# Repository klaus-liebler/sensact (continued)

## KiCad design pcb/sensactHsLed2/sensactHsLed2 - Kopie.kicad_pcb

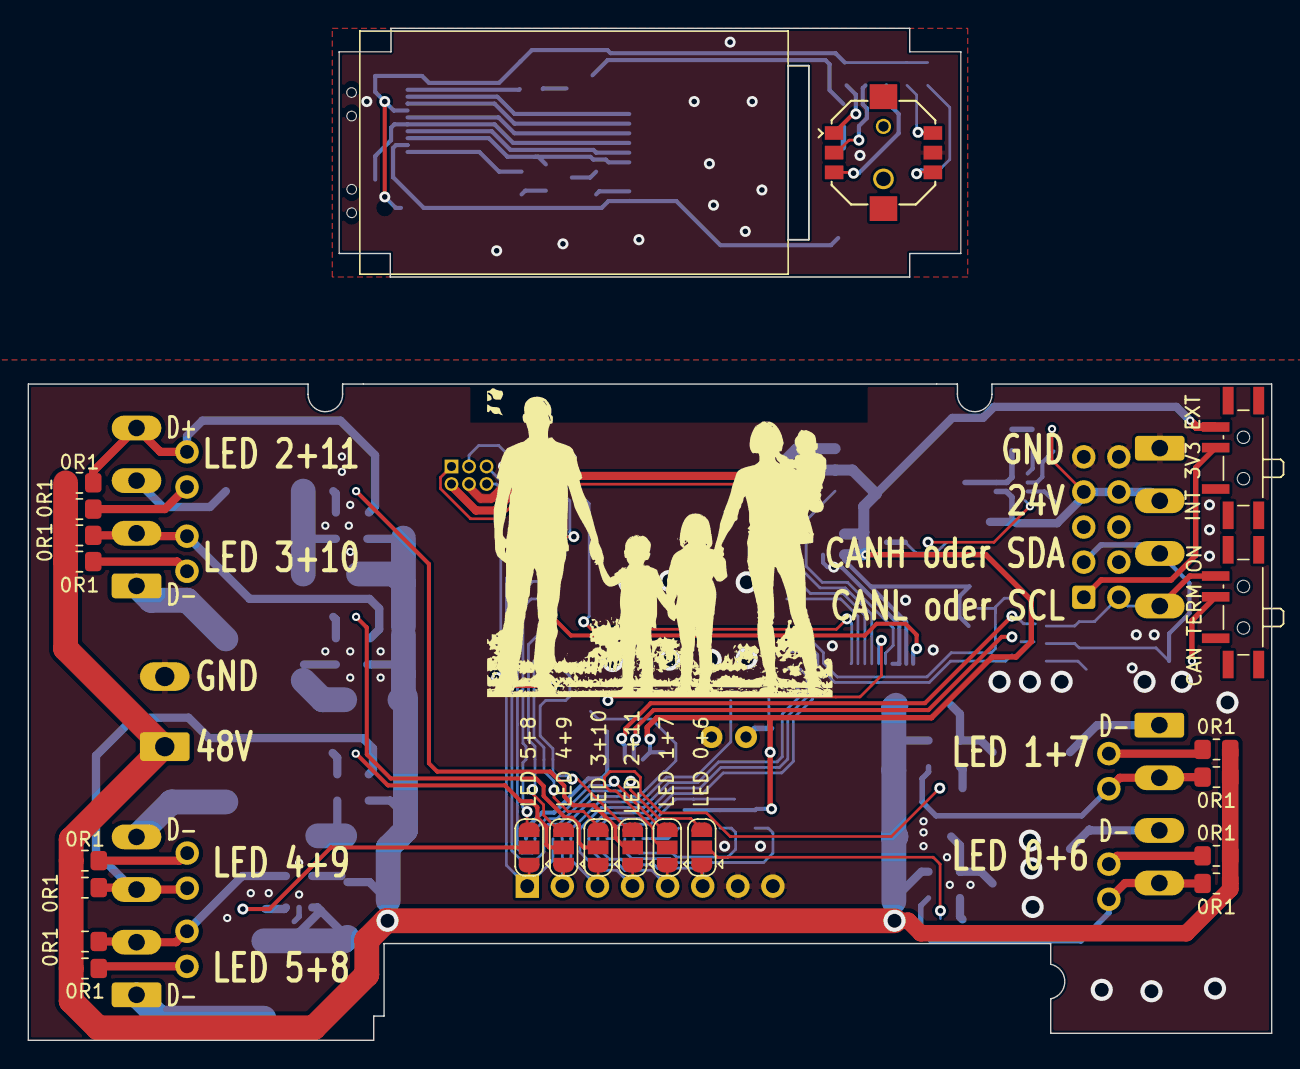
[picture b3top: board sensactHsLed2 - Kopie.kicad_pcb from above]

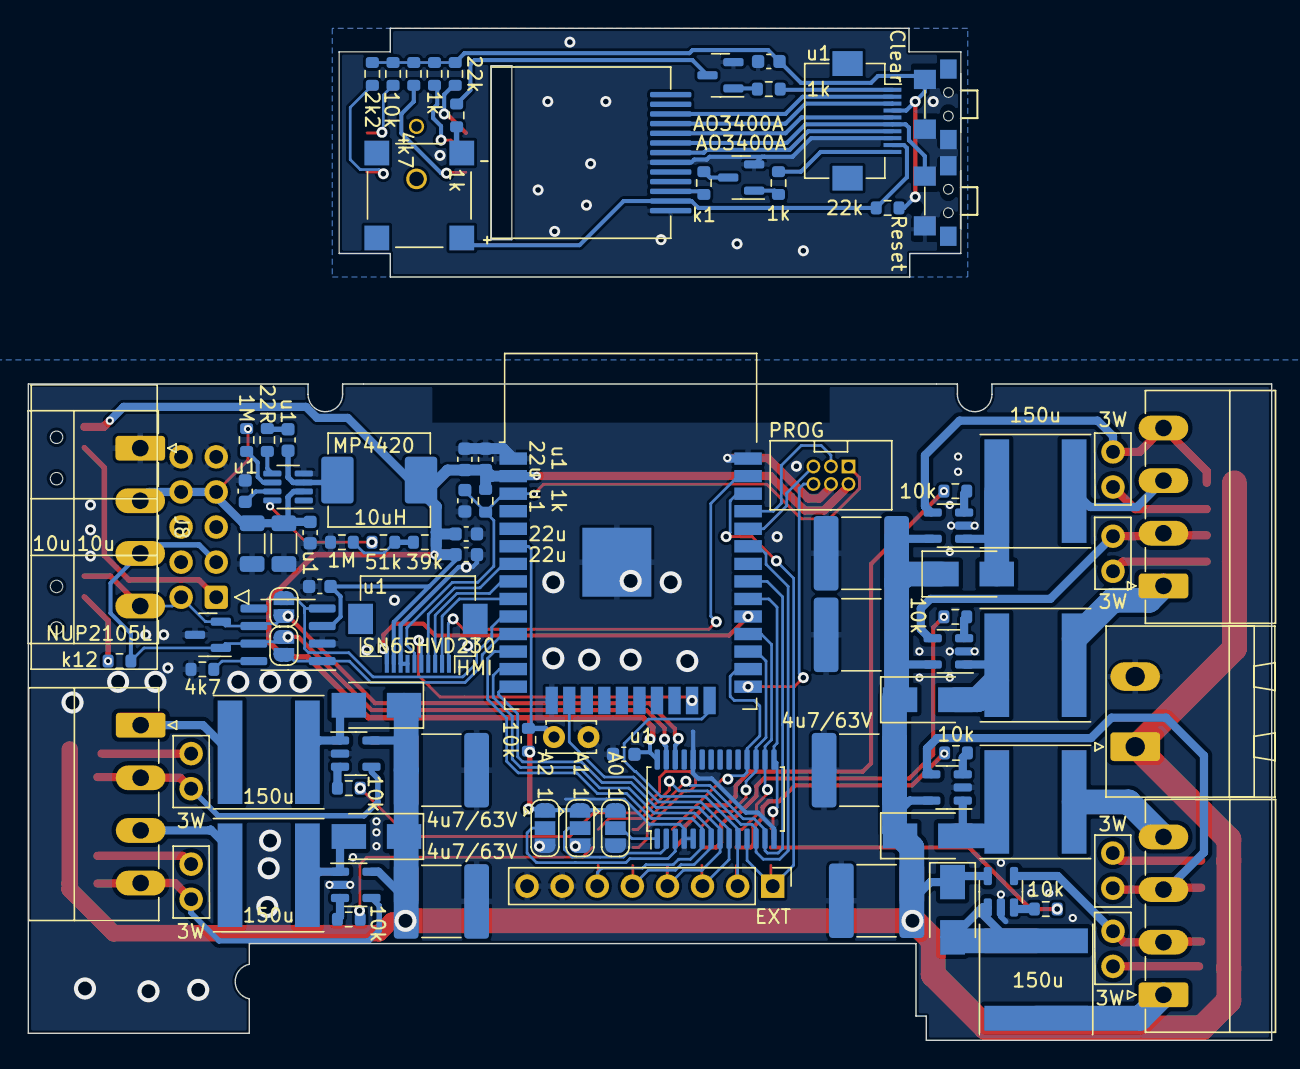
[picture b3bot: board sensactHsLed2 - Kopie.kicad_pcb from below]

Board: 2 copper layers, 90.0 x 47.5 mm, 118 parts (95 on the bottom side), 101 nets.

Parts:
BZ1: Buzzer; XDCR_CMT-7525-80-SMT-TR
C1, C10, C11: 22u; C_0603_1608Metric
C2, C3, C4, C7, C8, C9, C18, C19: u1; C_0603_1608Metric
C5, C6: 10u; C_1206_3216Metric
C12, C13, C14, C15, C16, C17: 4u7/63V; C_2220_5650Metric
D1: NUP2105L; SOT-23
D2, D3, D4, D5, D6, D7: D; D_SMA
IMG1: Family; family
J1: PROG; IDC_2x03_P1.27mm_Vertical
J2: EXT; PinHeader_1x08_P2.54mm_Vertical
J3, J4, J5: LED1+2; PhoenixContact_MC_1,5_4-G-3.81_1x04_P3.81mm_Horizontal
J6: Conn_01x02; PhoenixContact_MSTBA_2,5_2-G-5,08_1x02_P5.08mm_Horizontal
J7: SensactBusConnector; IDC-Header_2x05_P2.54mm_Horizontal
J8: POWER+CAN; PhoenixContact_MC_1,5_4-G-3.81_1x04_P3.81mm_Horizontal
J9: HMI; Hirose_FH12-10S-0.5SH_1x10-1MP_P0.50mm_Horizontal
J10: Conn_01x10; Hirose_FH12-10S-0.5SH_1x10-1MP_P0.50mm_Horizontal
JP1, JP2, JP3, JP4, JP5, JP6: 3W; Jumper 2x2.54
JP7: LED 0+6; SolderJumper-3_P1.3mm_Open_RoundedPad1.0x1.5mm
JP8: LED 1+7; SolderJumper-3_P1.3mm_Open_RoundedPad1.0x1.5mm
JP9: LED 2+11; SolderJumper-3_P1.3mm_Open_RoundedPad1.0x1.5mm
JP10: LED 3+10; SolderJumper-3_P1.3mm_Open_RoundedPad1.0x1.5mm
JP11: LED 4+9; SolderJumper-3_P1.3mm_Open_RoundedPad1.0x1.5mm
JP12: LED 5+8; SolderJumper-3_P1.3mm_Open_RoundedPad1.0x1.5mm
JP13, JP14: Jumper_2_Open; SolderJumper-2_P1.3mm_Open_RoundedPad1.0x1.5mm
L1: 10uH; L_Abracon_ASPI-0630LR
L2, L3, L4, L5, L6, L7: 150u; L_Taiyo-Yuden_NR-80xx
Q1, Q3: AO3400A; SOT-23
R1, R27, R34, R36, R37: 1k; R_0603_1608Metric
R2, R32: 4k7; R_0603_1608Metric
R3: k12; R_0603_1608Metric
R4, R7: 1M; R_0603_1608Metric
R5: 22R; R_0603_1608Metric
R6: 51k; R_0603_1608Metric
R8: 39k; R_0603_1608Metric
R9, R11, R13, R15, R17, R19, R31, R39: 10k; R_0603_1608Metric
R10, R12, R14, R16, R18, R20, R21, R22, R23, R24, R25, R26: 0R1; R_0805_2012Metric_Pad1.20x1.40mm_HandSolder
R28: k1; R_0603_1608Metric
R29, R30: 22k; R_0603_1608Metric
R33: 2k2; R_0603_1608Metric
S1: ALPS_SKRHABE010; Alps_SKRHABE010
SW1: Reset; Button_2x4x3,5_handsolder
SW2: CAN TERM ON; SW_SPDT_PCM12_handsolder
SW3: INT 3V3 EXT; SW_SPDT_PCM12_handsolder
SW4: A0 1; SolderJumper-3_P1.3mm_Open_RoundedPad1.0x1.5mm
SW5: A1 1; SolderJumper-3_P1.3mm_Open_RoundedPad1.0x1.5mm
SW6: A2 1; SolderJumper-3_P1.3mm_Open_RoundedPad1.0x1.5mm
SW7: Clear; Button_2x4x3,5_handsolder
TH1: Thermistor_NTC; C_Disc_D3.4mm_W2.1mm_P2.50mm
U1: SN65HVD230; SOIC-8_3.9x4.9mm_P1.27mm
U2: ESP32-WROOM-32
U3: MP4420; TSOT-23-8
U4: PCA9685PW; TSSOP-28_4.4x9.7mm_P0.65mm
U5, U6, U7, U8, U9, U10: ZXLD1362; SOT-23-5
X1: LH114; FP-114 13pol

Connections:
+3.3VP: BZ1.P (-), J10.9, R29.1, X1.12 (LEDA)
+3V3: C1.1, C2.1, C3.1, C10.1, C11.1, C18.1, J1.2, J9.9, L1.2, R1.1, R8.2, R39.1, SW3.3 (C), SW4.1 (A), SW5.1 (A), SW6.1 (A), U1.3 (VCC), U2.2 (VDD), U4.28 (VDD)
+24V: C5.1, C6.1, C7.1, J7.7 (24V), J7.8 (24V), J8.2, R4.1, U3.2 (VIN)
+48V: C12.2, C13.2, C14.2, C15.2, C16.2, C17.2, D2.1 (K), D3.1 (K), D4.1 (K), D5.1 (K), D6.1 (K), D7.1 (K), J6.1, R10.1, R12.1, R14.1, R16.1, R18.1, R20.1, R21.1, R22.1, R23.1, R24.1, R25.1, R26.1, U5.5 (VIN), U6.5 (VIN), U7.5 (VIN), U8.5 (VIN), U9.5 (VIN), U10.5 (VIN)
/LED_DRIVER1/D+: J3.2, JP1.2 (B), R10.2, U5.4 (Isense)
/LED_DRIVER1/D-: J3.1, L2.1
/LED_DRIVER1/LX: D2.2 (A), L2.2, U5.1 (LX)
/LED_DRIVER1/PWM: JP12.2 (C), R9.1
/LED_DRIVER1/R_sense: JP1.1 (A), R21.2
/LED_DRIVER2/D+: J3.3, JP2.2 (B), R12.2, U6.4 (Isense)
/LED_DRIVER2/D-: J3.4, L3.1
/LED_DRIVER2/LX: D3.2 (A), L3.2, U6.1 (LX)
/LED_DRIVER2/PWM: JP11.2 (C), R11.1
/LED_DRIVER2/R_sense: JP2.1 (A), R22.2
/LED_DRIVER3/D+: J4.2, JP3.2 (B), R14.2, U7.4 (Isense)
/LED_DRIVER3/D-: J4.1, L4.1
/LED_DRIVER3/LX: D4.2 (A), L4.2, U7.1 (LX)
/LED_DRIVER3/PWM: JP10.2 (C), R13.1
/LED_DRIVER3/R_sense: JP3.1 (A), R23.2
/LED_DRIVER4/D+: J4.4, JP4.2 (B), R16.2, U8.4 (Isense)
/LED_DRIVER4/D-: J4.3, L5.1
/LED_DRIVER4/LX: D5.2 (A), L5.2, U8.1 (LX)
/LED_DRIVER4/PWM: JP9.2 (C), R15.1
/LED_DRIVER4/R_sense: JP4.1 (A), R24.2
/LED_DRIVER5/D+: J5.2, JP5.2 (B), R18.2, U9.4 (Isense)
/LED_DRIVER5/D-: J5.1, L6.1
/LED_DRIVER5/LX: D6.2 (A), L6.2, U9.1 (LX)
/LED_DRIVER5/PWM: JP8.2 (C), R17.1
/LED_DRIVER5/R_sense: JP5.1 (A), R25.2
/LED_DRIVER6/D+: J5.4, JP6.2 (B), R20.2, U10.4 (Isense)
/LED_DRIVER6/D-: J5.3, L7.1
/LED_DRIVER6/LX: D7.2 (A), L7.2, U10.1 (LX)
/LED_DRIVER6/PWM: JP7.2 (C), R19.1
/LED_DRIVER6/R_sense: JP6.1 (A), R26.2
/SW: C9.2, L1.1, U3.3 (SW)
/THERM: R39.2, TH1.1, U2.6 (IO34)
/top_hmi/BACKLIGHT: J10.10, R27.1
/top_hmi/BUZZER: J10.1, R36.1
/top_hmi/CS: J10.7, X1.7 (~CS)
/top_hmi/MOSI: J10.2, X1.3 (SDA)
/top_hmi/RESET: J10.6, SW1.1, X1.6 (RES)
/top_hmi/RS: J10.5, X1.5 (RS)
/top_hmi/SCLK: J10.3, X1.4 (SCL)
/top_hmi/SW: C19.1, J10.4, R29.2, R30.1, R31.1, R32.1, R33.1, R34.1, SW7.1
A0: SW4.2 (B), U4.1 (A0)
A1: SW5.2 (B), U4.2 (A1)
A2: SW6.2 (B), U4.3 (A2)
BACKLIGHT: J9.10, U2.29 (IO5)
BUZZER: J9.1, U2.37 (IO23)
CANH_SDA: D1.1 (K), J7.3 (SDA), J8.3, JP13.2 (B), R3.1, U1.7 (CANH), U4.27 (SDA)
CANL_SCL: D1.2 (K), J7.2 (SCL), J8.4, JP14.2 (B), SW2.3 (C), U1.6 (CANL), U4.26 (SCL)
CAN_RX: JP14.1 (A), U1.4 (R), U2.10 (IO25)
CAN_TX: JP13.1 (A), U1.1 (D), U2.11 (IO26)
GND: C1.2, C2.2, C3.2, C4.2, C5.2, C6.2, C7.2, C8.2, C10.2, C11.2, C12.1, C13.1, C14.1, C15.1, C16.1, C17.1, C18.2, D1.3 (A), J1.4, J2.7, J2.8, J6.2, J7.9 (GND), J7.10 (GND), J8.1, J9.7, J9.8, R2.2, R7.2, SW4.3 (C), SW5.3 (C), SW6.3 (C), TH1.2, U1.2 (GND), U2.1 (GND), U2.15 (GND), U2.38 (GND), U2.39 (GND), U3.4 (GND), U4.4 (A3), U4.5 (A4), U4.14 (VSS), U4.24 (A5), U5.2 (GND), U6.2 (GND), U7.2 (GND), U8.2 (GND), U9.2 (GND), U10.2 (GND)
GND1: C19.2, J10.8, Q1.2 (S), Q3.2 (S), S1.5 (COM), SW1.2, SW7.2, X1.8 (GND), X1.13 (GND)
LED0: J2.6, JP7.1 (A), U2.12 (IO27), U4.6 (LED0)
LED1: J2.5, JP8.1 (A), U2.13 (IO14), U4.7 (LED1)
LED2: J2.4, JP9.1 (A), U2.14 (IO12), U4.8 (LED2)
LED3: J2.3, JP10.1 (A), U2.16 (IO13), U4.9 (LED3)
LED4: J2.2, JP11.1 (A), U2.24 (IO2), U4.10 (LED4)
LED5: J2.1, JP12.1 (A), U2.36 (IO22), U4.11 (LED5)
LED6: JP7.3 (B), U2.33 (IO21), U4.12 (LED6)
LED7: JP8.3 (B), U2.31 (IO19), U4.13 (LED7)
LED8: JP12.3 (B), U2.30 (IO18), U4.15 (LED8)
LED9: JP11.3 (B), U2.28 (IO17), U4.16 (LED9)
LED10: JP10.3 (B), U2.27 (IO16), U4.17 (LED10)
LED11: JP9.3 (B), U2.26 (IO4), U4.18 (LED11)
MOSI: J9.2, U2.9 (IO33)
unnamed: BZ1.N (+), R37.2
unnamed: C8.1, U3.7 (VCC)
unnamed: C9.1, R5.1
unnamed: J7.1 (3V3), SW3.2 (B)
unnamed: Q1.1 (G), R27.2
unnamed: Q1.3 (D), R28.1
unnamed: Q3.1 (G), R36.2
unnamed: Q3.3 (D), R37.1
unnamed: R2.1, U1.8 (Rs)
unnamed: R3.2, SW2.2 (B)
unnamed: R4.2, U3.6 (EN/SYNC)
unnamed: R5.2, U3.5 (BST)
unnamed: R6.1, U3.8 (FB)
unnamed: R6.2, R7.1, R8.1
unnamed: R9.2, U5.3 (ADJ)
unnamed: R11.2, U6.3 (ADJ)
unnamed: R13.2, U7.3 (ADJ)
unnamed: R15.2, U8.3 (ADJ)
unnamed: R17.2, U9.3 (ADJ)
unnamed: R19.2, U10.3 (ADJ)
unnamed: R28.2, X1.11 (LEDK)
unnamed: R30.2, S1.1 (A)
unnamed: R31.2, S1.4 (B)
unnamed: R32.2, S1.3 (C)
unnamed: R33.2, S1.6 (D)
unnamed: R34.2, S1.2 (CTR)
PROG_IO0: J1.6, U2.25 (IO0)
PROG_RX: J1.5, U2.34 (RXD0/IO3)
PROG_TX: J1.3, U2.35 (TXD0/IO1)
RESET: C4.1, J1.1, J9.6, R1.2, U2.3 (EN)
RS: J9.5, U2.23 (IO15)
SCLK: J9.3, U2.8 (IO32)
SW1: J9.4, U2.7 (IO35)

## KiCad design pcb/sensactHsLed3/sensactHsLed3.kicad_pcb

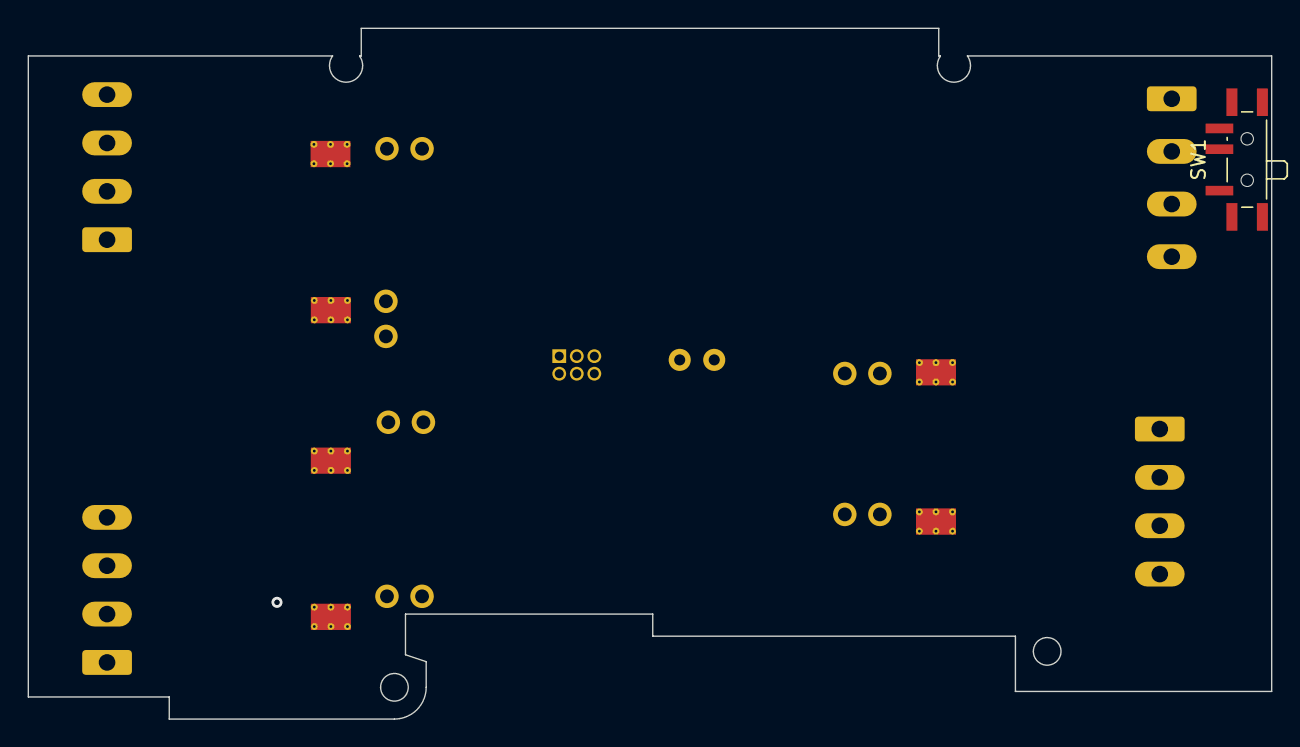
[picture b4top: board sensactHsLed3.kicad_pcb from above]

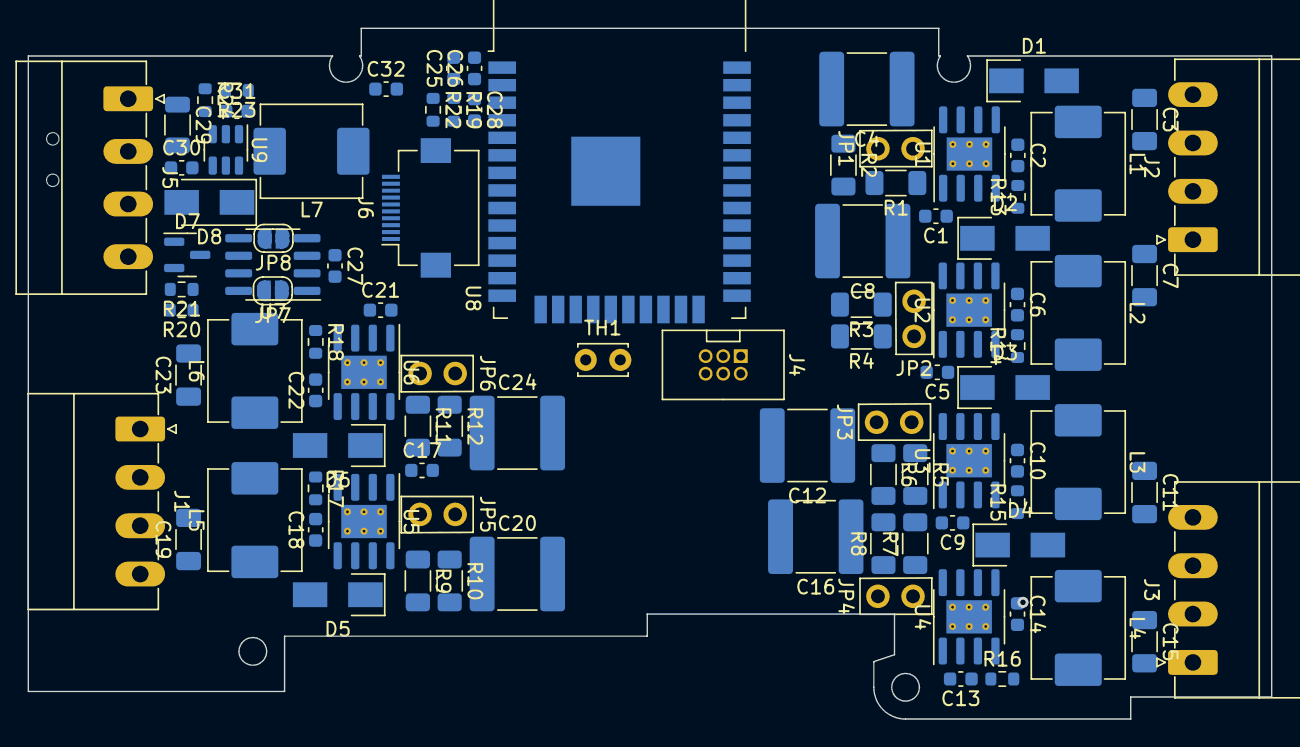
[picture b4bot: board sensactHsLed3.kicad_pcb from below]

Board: 2 copper layers, 90.0 x 50.0 mm, 96 parts (95 on the bottom side), 67 nets, no tracks yet.

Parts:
C1, C5, C9, C13, C17, C21: 1n/25V; C_0603_1608Metric
C2, C6, C10, C14, C18, C22: 1u/25V; C_0603_1608Metric
C3, C7, C11, C15, C19, C23: 10u/50V; C_1206_3216Metric_Pad1.33x1.80mm_HandSolder
C4, C8, C12, C16, C20, C24: 10u/100V; C_2220_5650Metric
C25, C32: 22u; C_0603_1608Metric
C26, C27, C28, C30: u1; C_0603_1608Metric
C29: 10u; C_1206_3216Metric
C31: 10n; C_0603_1608Metric
D1, D2, D3, D4, D5, D6: SS210; D_SMA
D7: NUP2105L; SOT-23
D8: SS34; D_SMA
J1, J2, J3: Conn_01x04; PhoenixContact_MC_1,5_4-G-3.5_1x04_P3.50mm_Horizontal
J4: PROG; IDC_2x03_P1.27mm_Vertical
J5: POWER+CAN; PhoenixContact_MC_1,5_4-G-3.81_1x04_P3.81mm_Horizontal
J6: HMI; Hirose_FH12-10S-0.5SH_1x10-1MP_P0.50mm_Horizontal
JP1, JP2, JP3, JP4, JP5, JP6: 3W; Jumper 2x2.54
JP7, JP8: Jumper_2_Open; SolderJumper-2_P1.3mm_Open_RoundedPad1.0x1.5mm
L1, L2, L3, L4, L5, L6: 47u; L_Abracon_ASPI-0630LR
L7: 6u8; L_Abracon_ASPI-0630LR
R1, R3, R5, R7, R9, R11: 0R66; R_1206_3216Metric_Pad1.30x1.75mm_HandSolder
R2, R4, R6, R8, R10, R12: 0R5; R_1206_3216Metric_Pad1.30x1.75mm_HandSolder
R13, R14, R15, R16, R17, R18, R22: 10k; R_0603_1608Metric
R19: 1k; R_0603_1608Metric
R20: 4k7; R_0603_1608Metric
R21: k12; R_0603_1608Metric
R23: 68k; R_0603_1608Metric
R24: 13k; R_0603_1608Metric
SW1: CAN TERM ON; SW_SPDT_PCM12_handsolder
TH1: Thermistor_NTC; C_Disc_D3.4mm_W2.1mm_P2.50mm
U1, U2, U3, U4, U5, U6: BP1808; SOIC-8-1EP_3.9x4.9mm_P1.27mm_EP2.41x3.3mm_ThermalVias
U7: SN65HVD230; SOIC-8_3.9x4.9mm_P1.27mm
U8: ESP32-WROOM-32
U9: EUP3458; SOT-23-6

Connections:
+3V3: C25.1, C26.1, C27.1, J4.2, J6.9, R19.1, R22.1, U7.3 (VCC), U8.2 (VDD)
+5V: C32.1, L7.1, R23.1
+24V: C29.2, C30.2, J5.2, U9.4 (~SHDN), U9.5 (VIN)
+48V: C4.1, C8.1, C12.1, C16.1, C20.1, C24.1, D1.1 (K), D2.1 (K), D3.1 (K), D4.1 (K), D5.1 (K), D6.1 (K), R1.2, R2.2, R3.2, R4.2, R5.2, R6.2, R7.2, R8.2, R9.2, R10.2, R11.2, R12.2, U1.7 (VOUT), U2.7 (VOUT), U3.7 (VOUT), U4.7 (VOUT), U5.7 (VOUT), U6.7 (VOUT)
/LED_DRV1/COMP: C5.1, U2.2 (COMP)
/LED_DRV1/CS: C7.1, JP2.2 (B), R3.1, U2.8 (CS)
/LED_DRV1/DIM: R14.1, U2.3 (DIM)
/LED_DRV1/LED-: C7.2, L2.2
/LED_DRV1/SW: D2.2 (A), L2.1, U2.5 (SW)
/LED_DRV2/COMP: C9.1, U3.2 (COMP)
/LED_DRV2/CS: C11.1, JP3.2 (B), R5.1, U3.8 (CS)
/LED_DRV2/DIM: R15.1, U3.3 (DIM)
/LED_DRV2/LED-: C11.2, L3.2
/LED_DRV2/SW: D3.2 (A), L3.1, U3.5 (SW)
/LED_DRV3/COMP: C13.1, U4.2 (COMP)
/LED_DRV3/CS: C15.1, JP4.2 (B), R7.1, U4.8 (CS)
/LED_DRV3/DIM: R16.1, U4.3 (DIM)
/LED_DRV3/LED-: C15.2, L4.2
/LED_DRV3/SW: D4.2 (A), L4.1, U4.5 (SW)
/LED_DRV4/COMP: C17.1, U5.2 (COMP)
/LED_DRV4/CS: C19.1, JP5.2 (B), R9.1, U5.8 (CS)
/LED_DRV4/DIM: R17.1, U5.3 (DIM)
/LED_DRV4/LED-: C19.2, L5.2
/LED_DRV4/SW: D5.2 (A), L5.1, U5.5 (SW)
/LED_DRV5/COMP: C21.1, U6.2 (COMP)
/LED_DRV5/CS: C23.1, JP6.2 (B), R11.1, U6.8 (CS)
/LED_DRV5/DIM: R18.1, U6.3 (DIM)
/LED_DRV5/LED-: C23.2, L6.2
/LED_DRV5/SW: D6.2 (A), L6.1, U6.5 (SW)
/LED_DRV/COMP: C1.1, U1.2 (COMP)
/LED_DRV/CS: C3.1, JP1.2 (B), R1.1, U1.8 (CS)
/LED_DRV/DIM: R13.1, U1.3 (DIM)
/LED_DRV/LED-: C3.2, L1.2
/LED_DRV/SW: D1.2 (A), L1.1, U1.5 (SW)
/SW: C31.2, D8.1 (K), L7.2, U9.6 (SW)
/THERM: R22.2, TH1.1, U8.6 (IO34)
BACKLIGHT: J6.10, U8.29 (IO5)
BUZZER: J6.1, U8.23 (IO15)
CANH_SDA: D7.1 (K), J5.3, JP7.2 (B), R21.1, U7.7 (CANH)
CANL_SCL: D7.2 (K), J5.4, JP8.2 (B), SW1.3 (C), U7.6 (CANL)
CAN_RX: JP8.1 (A), U7.4 (R), U8.7 (IO35)
CAN_TX: JP7.1 (A), U7.1 (D), U8.8 (IO32)
GND: C1.2, C2.2, C4.2, C5.2, C6.2, C8.2, C9.2, C10.2, C12.2, C13.2, C14.2, C16.2, C17.2, C18.2, C20.2, C21.2, C22.2, C24.2, C25.2, C26.2, C27.2, C28.2, C29.1, C30.1, C32.2, D7.3 (A), D8.2 (A), J4.4, J5.1, J6.7, J6.8, R13.2, R14.2, R15.2, R16.2, R17.2, R18.2, R20.2, R24.1, TH1.2, U1.1 (OVP), U1.4 (GND), U1.9 (PAD), U2.1 (OVP), U2.4 (GND), U2.9 (PAD), U3.1 (OVP), U3.4 (GND), U3.9 (PAD), U4.1 (OVP), U4.4 (GND), U4.9 (PAD), U5.1 (OVP), U5.4 (GND), U5.9 (PAD), U6.1 (OVP), U6.4 (GND), U6.9 (PAD), U7.2 (GND), U8.1 (GND), U8.15 (GND), U8.38 (GND), U8.39 (GND), U9.2 (GND)
MOSI: J6.2, U8.37 (IO23)
unnamed: C2.1, U1.6 (VDD)
unnamed: C6.1, U2.6 (VDD)
unnamed: C10.1, U3.6 (VDD)
unnamed: C14.1, U4.6 (VDD)
unnamed: C18.1, U5.6 (VDD)
unnamed: C22.1, U6.6 (VDD)
unnamed: C31.1, U9.1 (CB)
unnamed: JP1.1 (A), R2.1
unnamed: JP2.1 (A), R4.1
unnamed: JP3.1 (A), R6.1
unnamed: JP4.1 (A), R8.1
unnamed: JP5.1 (A), R10.1
unnamed: JP6.1 (A), R12.1
unnamed: R20.1, U7.8 (Rs)
unnamed: R21.2, SW1.2 (B)
unnamed: R23.2, R24.2, U9.3 (FB)
PROG_IO0: J4.6, U8.25 (IO0)
PROG_RX: J4.5, U8.34 (RXD0/IO3)
PROG_TX: J4.3, U8.35 (TXD0/IO1)
RESET: C28.1, J4.1, J6.6, R19.2, U8.3 (EN)
RS: J6.5, U8.36 (IO22)
SCLK: J6.3, U8.30 (IO18)
SW1: J6.4, U8.4 (SENSOR_VP)

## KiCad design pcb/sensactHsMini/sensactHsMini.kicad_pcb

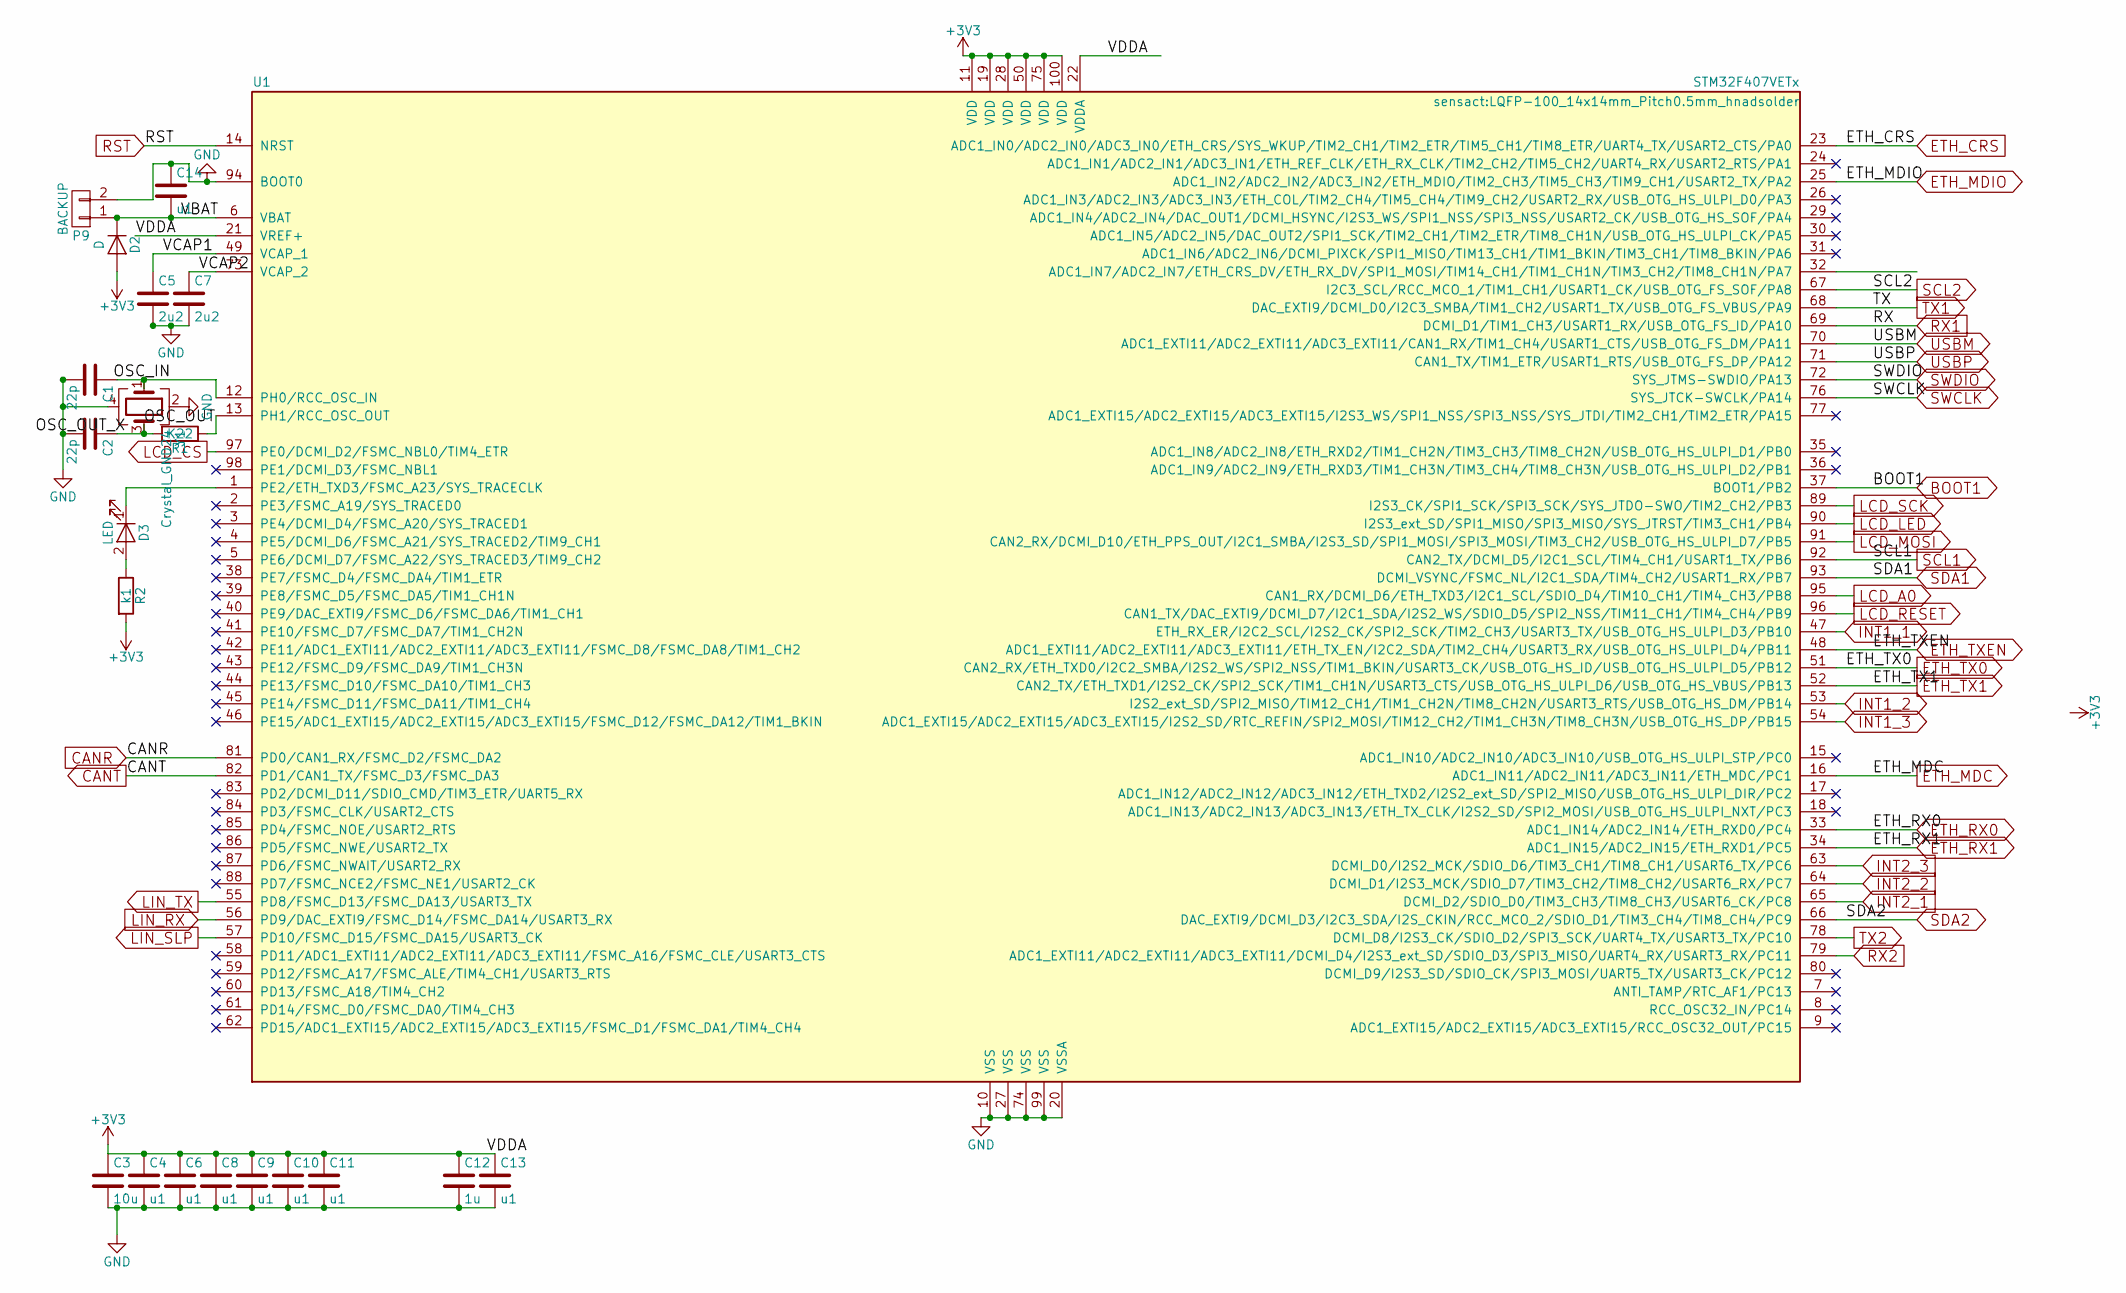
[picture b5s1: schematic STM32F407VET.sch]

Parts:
C1, C2: 22p; C_0805_HandSoldering
C3: 10u; C_1206_HandSoldering
C4, C6, C8, C9, C10, C11, C13, C14: u1; C_0805_HandSoldering
C5, C7: 2u2; C_0805_HandSoldering
C12: 1u; C_0805_HandSoldering
D2: D; sod123_handsolder
D3: LED; R_0805_HandSoldering
P9: BACKUP; Pin_Header_Straight_1x02_Pitch2.54mm
R1: K22; R_0805_HandSoldering
R2: k1; R_0805_HandSoldering
U1: STM32F407VETx; LQFP-100_14x14mm_Pitch0.5mm_hnadsolder
Y1: Crystal_GND24; quartz3225

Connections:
+3V3: C3.1, C4.1, C6.1, C8.1, C9.1, C10.1, C11.1, C12.1, C13.1, D2.2 (A), R2.2, U1.11 (VDD), U1.19 (VDD), U1.21 (VREF+), U1.22 (VDDA), U1.28 (VDD), U1.50 (VDD), U1.75 (VDD), U1.100 (VDD); also elsewhere on the board
/STM32F407VET/OSC_IN: C1.1, U1.12 (PH0/RCC_OSC_IN), Y1.1
/STM32F407VET/OSC_OUT: R1.1, U1.13 (PH1/RCC_OSC_OUT)
/STM32F407VET/OSC_OUT_X: C2.1, R1.2, Y1.3
/STM32F407VET/VBAT: C14.2, D2.1 (K), P9.1, U1.6 (VBAT)
/STM32F407VET/VCAP1: C5.1, U1.49 (VCAP_1)
/STM32F407VET/VCAP2: C7.1, U1.73 (VCAP_2)
CANR: U1.81 (PD0/CAN1_RX/FSMC_D2/FSMC_DA2); also elsewhere on the board
CANT: U1.82 (PD1/CAN1_TX/FSMC_D3/FSMC_DA3); also elsewhere on the board
ETH_CRS: U1.23 (ADC1_IN0/ADC2_IN0/ADC3_IN0/ETH_CRS/SYS_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); also elsewhere on the board
ETH_MDC: U1.16 (ADC1_IN11/ADC2_IN11/ADC3_IN11/ETH_MDC/P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); also elsewhere on the board
ETH_MDIO: U1.25 (ADC1_IN2/ADC2_IN2/ADC3_IN2/ETH_MDIO/TIM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); also elsewhere on the board
ETH_RX0: U1.33 (ADC1_IN14/ADC2_IN14/ETH_RXD0/PC4); also elsewhere on the board
ETH_RX1: U1.34 (ADC1_IN15/ADC2_IN15/ETH_RXD1/PC5); also elsewhere on the board
ETH_TX0: U1.51 (CAN2_RX/ETH_TXD0/I2C2_SMBA/I2S2_WS/SPI2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); also elsewhere on the board
ETH_TX1: U1.52 (CAN2_TX/ETH_TXD1/I2S2_CK/SPI2_SCK/TIM1_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); also elsewhere on the board
ETH_TXEN: U1.48 (ADC1_EXTI11/ADC2_EXTI11/ADC3_EXTI11/ETH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); also elsewhere on the board
GND: C1.2, C2.2, C3.2, C4.2, C5.2, C6.2, C7.2, C8.2, C9.2, C10.2, C11.2, C12.2, C13.2, C14.1, P9.2, U1.10 (VSS), U1.20 (VSSA), U1.27 (VSS), U1.74 (VSS), U1.94 (BOOT0), U1.99 (VSS), Y1.2, Y1.4; also elsewhere on the board
INT1_1: U1.47 (ETH_RX_ER/I2C2_SCL/I2S2_CK/SPI2_SCK/TIM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); also elsewhere on the board
INT1_2: U1.53 (I2S2_ext_SD/SPI2_MISO/TIM12_CH1/TIM1_CH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); also elsewhere on the board
INT1_3: U1.54 (ADC1_EXTI15/ADC2_EXTI15/ADC3_EXTI15/I2S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); also elsewhere on the board
INT2_1: U1.65 (DCMI_D2/SDIO_D0/TIM3_CH3/TIM8_CH3/USART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); also elsewhere on the board
INT2_2: U1.64 (DCMI_D1/I2S3_MCK/SDIO_D7/TIM3_CH2/TIM8_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); also elsewhere on the board
INT2_3: U1.63 (DCMI_D0/I2S2_MCK/SDIO_D6/TIM3_CH1/TIM8_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); also elsewhere on the board
LCD_A0: U1.95 (CAN1_RX/DCMI_D6/ETH_TXD3/I2C1_SCL/SDIO_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); also elsewhere on the board
LCD_CS: U1.97 (PE0/DCMI_D2/FSMC_NBL0/TIM4_ETR); also elsewhere on the board
LCD_LED: U1.90 (I2S3_ext_SD/SPI1_MISO/SPI3_MISO/SYS_JTR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); also elsewhere on the board
LCD_MOSI: U1.91 (CAN2_RX/DCMI_D10/ETH_PPS_OUT/I2C1_SMBA/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); also elsewhere on the board
LCD_RESET: U1.96 (CAN1_TX/DAC_EXTI9/DCMI_D7/I2C1_SDA/I2S2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); also elsewhere on the board
LCD_SCK: U1.89 (I2S3_CK/SPI1_SCK/SPI3_SCK/SYS_JTDO-SWO/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); also elsewhere on the board
LIN_RX: U1.56 (PD9/DAC_EXTI9/FSMC_D14/FSMC_DA14/USART3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); also elsewhere on the board
LIN_SLP: U1.57 (PD10/FSMC_D15/FSMC_DA15/USART3_CK); also elsewhere on the board
LIN_TX: U1.55 (PD8/FSMC_D13/FSMC_DA13/USART3_TX); also elsewhere on the board
unnamed: D3.1 (K), U1.1 (PE2/ETH_TXD3/FSMC_A23/SYS_TRACECLK)
unnamed: D3.2 (A), R2.1
RST: U1.14 (NRST); also elsewhere on the board
RX1: U1.69 (DCMI_D1/TIM1_CH3/USART1_RX/USB_OTG_FS_I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); also elsewhere on the board
RX2: U1.79 (ADC1_EXTI11/ADC2_EXTI11/ADC3_EXTI11/DCM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); also elsewhere on the board
SCL1: U1.92 (CAN2_TX/DCMI_D5/I2C1_SCL/TIM4_CH1/USART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); also elsewhere on the board
SCL2: U1.67 (I2C3_SCL/RCC_MCO_1/TIM1_CH1/USART1_CK/U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); also elsewhere on the board
SDA1: U1.93 (DCMI_VSYNC/FSMC_NL/I2C1_SDA/TIM4_CH2/US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); also elsewhere on the board
SDA2: U1.66 (DAC_EXTI9/DCMI_D3/I2C3_SDA/I2S_CKIN/RCC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); also elsewhere on the board
SWCLK: U1.76 (SYS_JTCK-SWCLK/PA14); also elsewhere on the board
SWDIO: U1.72 (SYS_JTMS-SWDIO/PA13); also elsewhere on the board
TX1: U1.68 (DAC_EXTI9/DCMI_D0/I2C3_SMBA/TIM1_CH2/US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); also elsewhere on the board
TX2: U1.78 (DCMI_D8/I2S3_CK/SDIO_D2/SPI3_SCK/UART4_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); also elsewhere on the board

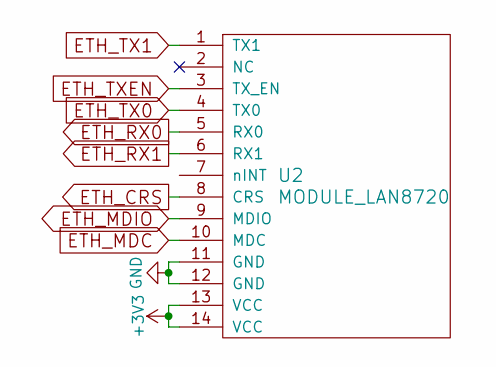
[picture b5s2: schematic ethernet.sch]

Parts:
U2: MODULE_LAN8720

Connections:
+3V3: U2.13 (VCC), U2.14 (VCC); also elsewhere on the board
ETH_CRS: U2.8 (CRS); also elsewhere on the board
ETH_MDC: U2.10 (MDC); also elsewhere on the board
ETH_MDIO: U2.9 (MDIO); also elsewhere on the board
ETH_RX0: U2.5 (RX0); also elsewhere on the board
ETH_RX1: U2.6 (RX1); also elsewhere on the board
ETH_TX0: U2.4 (TX0); also elsewhere on the board
ETH_TX1: U2.1 (TX1); also elsewhere on the board
ETH_TXEN: U2.3 (TX_EN); also elsewhere on the board
GND: U2.11 (GND), U2.12 (GND); also elsewhere on the board

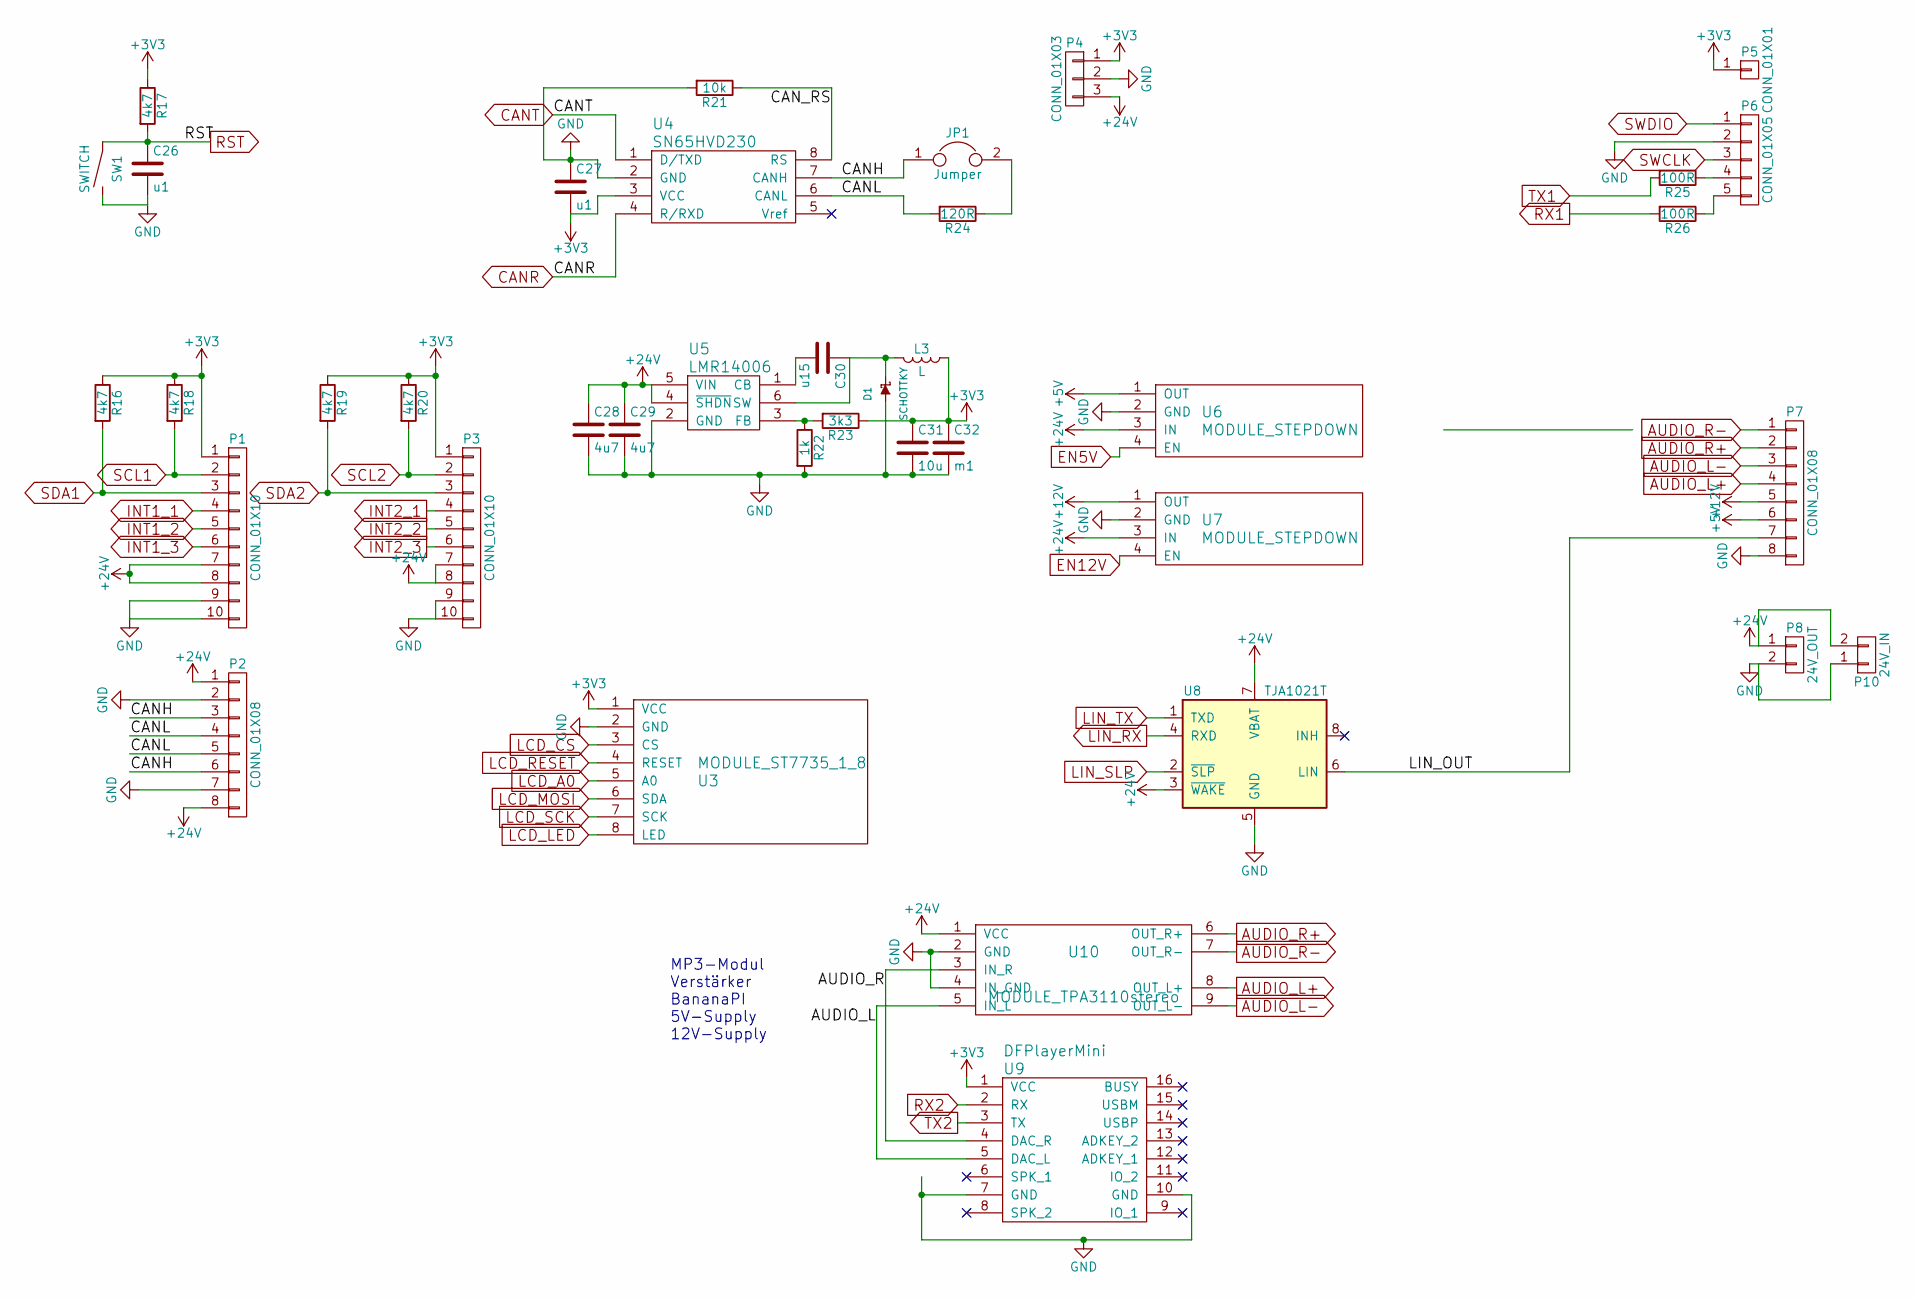
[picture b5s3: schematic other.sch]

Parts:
C26, C27: u1; C_0805_HandSoldering
C28, C29: 4u7; C_1206_HandSoldering
C30: u15; C_0805_HandSoldering
C31: 10u; C_1206_HandSoldering
C32: m1; C_1206_HandSoldering
D1: SCHOTTKY; do214ac_handsolder
JP1: Jumper; Pin_Header_Straight_1x02_Pitch2.54mm
L3: L; Inductor_CD104_handsolder
P1, P3: CONN_01X10; IDC_Header_Straight_10pins
P2, P7: CONN_01X08; KF141R-8p
P4: CONN_01X03; KF141R-3p
P5: CONN_01X01; Pin_Header_Straight_1x01_Pitch2.54mm
P6: CONN_01X05; miniusb_vert
P8: 24V_OUT; conn_2P
P10: 24V_IN; conn_2P
R16, R17, R18, R19, R20: 4k7; R_0805_HandSoldering
R21: 10k; R_0805_HandSoldering
R22: 1k; R_0805_HandSoldering
R23: 3k3; R_0805_HandSoldering
R24: 120R; R_1206_HandSoldering
R25, R26: 100R; R_0805_HandSoldering
SW1: SWITCH; SW_PUSH_6mm
U3: MODULE_ST7735_1_8; MODULE_ST7735_18
U4: SN65HVD230; SOIC-8_3.9x4.9mm_Pitch1.27mm_handsolder
U5: LMR14006; SOT-23-6_handsolder
U6, U7: MODULE_STEPDOWN
U8: TJA1021T; SOIC-8_3.9x4.9mm_Pitch1.27mm
U9: DFPlayerMini
U10: MODULE_TPA3110stereo

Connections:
+3V3: C27.2, C31.1, C32.1, L3.1, P1.1, P3.1, P4.1, P5.1, R16.1, R17.1, R18.1, R19.1, R20.1, R23.1, U3.1 (VCC), U4.3 (VCC), U9.1 (VCC); also elsewhere on the board
+5V: P7.6, U6.1 (OUT)
+12V: P7.5, U7.1 (OUT)
+24V: C28.1, C29.1, P1.7, P1.8, P2.1, P2.8, P3.7, P3.8, P4.3, P8.1, P10.2, U5.4 (~SHDN), U5.5 (VIN), U6.3 (IN), U7.3 (IN), U8.3 (~WAKE~), U8.7 (VBAT), U10.1 (VCC)
/other/AUDIO_L: U9.5 (DAC_L), U10.5 (IN_L)
/other/AUDIO_R: U9.4 (DAC_R), U10.3 (IN_R)
/other/CANH: JP1.1, P2.3, P2.6, U4.7 (CANH)
/other/CANL: P2.4, P2.5, R24.2, U4.6 (CANL)
/other/CAN_RS: R21.1, U4.8 (RS)
/other/LIN_OUT: P7.7, U8.6 (LIN)
AUDIO_L+: P7.4, U10.8 (OUT_L+)
AUDIO_L-: P7.3, U10.9 (OUT_L-)
AUDIO_R+: P7.2, U10.6 (OUT_R+)
AUDIO_R-: P7.1, U10.7 (OUT_R-)
CANR: U4.4 (R/RXD); also elsewhere on the board
CANT: U4.1 (D/TXD); also elsewhere on the board
GND: C26.2, C27.1, C28.2, C29.2, C31.2, C32.2, D1.1 (A), P1.9, P1.10, P2.2, P2.7, P3.9, P3.10, P4.2, P6.2, P7.8, P8.2, P10.1, R21.2, R22.2, SW1.2, U3.2 (GND), U4.2 (GND), U5.2 (GND), U6.2 (GND), U7.2 (GND), U8.5 (GND), U9.7 (GND), U9.10 (GND), U10.2 (GND), U10.4 (IN_GND); also elsewhere on the board
INT1_1: P1.4; also elsewhere on the board
INT1_2: P1.5; also elsewhere on the board
INT1_3: P1.6; also elsewhere on the board
INT2_1: P3.4; also elsewhere on the board
INT2_2: P3.5; also elsewhere on the board
INT2_3: P3.6; also elsewhere on the board
LCD_A0: U3.5 (A0); also elsewhere on the board
LCD_CS: U3.3 (CS); also elsewhere on the board
LCD_LED: U3.8 (LED); also elsewhere on the board
LCD_MOSI: U3.6 (SDA); also elsewhere on the board
LCD_RESET: U3.4 (RESET); also elsewhere on the board
LCD_SCK: U3.7 (SCK); also elsewhere on the board
LIN_RX: U8.4 (RXD); also elsewhere on the board
LIN_SLP: U8.2 (~SLP~); also elsewhere on the board
LIN_TX: U8.1 (TXD); also elsewhere on the board
unnamed: C30.1, D1.2 (K), L3.2, U5.6 (SW)
unnamed: C30.2, U5.1 (CB)
unnamed: JP1.2, R24.1
unnamed: P6.4, R25.1
unnamed: P6.5, R26.1
unnamed: R22.1, R23.2, U5.3 (FB)
RST: C26.1, R17.2, SW1.1; also elsewhere on the board
RX1: R26.2; also elsewhere on the board
RX2: U9.2 (RX); also elsewhere on the board
SCL1: P1.2, R18.2; also elsewhere on the board
SCL2: P3.2, R20.2; also elsewhere on the board
SDA1: P1.3, R16.2; also elsewhere on the board
SDA2: P3.3, R19.2; also elsewhere on the board
SWCLK: P6.3; also elsewhere on the board
SWDIO: P6.1; also elsewhere on the board
TX1: R25.2; also elsewhere on the board
TX2: U9.3 (TX); also elsewhere on the board

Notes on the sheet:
MP3-Modul Verstärker BananaPI 5V-Supply 12V-Supply
